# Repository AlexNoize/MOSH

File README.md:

# MOSH
#### Arduino Project in 5th year ISS at INSA Toulouse

## Overview
This repository contains the work produced during the course of Microcontroler and Open-Source Hardware (MOSH) of the 5th year Innovative Smart Systems (ISS) at INSA Toulouse. This work was produced by Alex Noize and Mathieu Raynaud.

The aim of this project was to design a complete PCB (Printed Circuit Board) implementing a double layer transimpedance amplificator assembly. This circuit is then used plugged to an Arduino board and a LoRa antenna to collect data from a gaz sensor and send it through a LoRa network. The project is located [here](https://github.com/AlexNoize/MOSH/tree/master/KiCad/Shield_Gas_Sensor/Shield_Gas_Sensor_Final)

## PCB schematic
Let's first have a look to the electrical circuit:

On the center of the image, the double layer transimpedance circuit implements several functionalities: 
* On the left of the scheme, the entry resistor (R1) protect the operational amplifier from the electrostatic discharges, and is associated to the C1 capacitor to filter the voltage noise.
* The C1 capacitor is also associated to the R2 resistor to filter the current noise.
* The R3 resistor is used to adapt our assembly to the correct calibre.
* At the output of the amplifier, the C2 capacitor is associated to the R4 resistor to create an active filter.
* Then, the R5 resistor and the C4 capacitor constitute a low-pass filter at the output of the assembly.
* Finally, the C3 capacitor filter the noise coming from the 5V voltage input.

We also have 3 other schemes on the picture which are:
* The RN2483 LoRa transceiver scheme on the left-top of the scheme
* The gas sensor scheme on the top of the scheme
* The Arduino Uno shield schematic on the right of the scheme
These components are required on the scheme because they need to be considered as soon as our PCB needs to communicate with them.

## PCB footprint on KiCad
Now, let's study the footprint generated with KiCad:

On the footprint above, we made the connections between all the needed pins of our board.

To be able to put our routes on only one face of the PCB, we had to add a ground layer on the entire surface of the PCB, so that we didn't need anymore to connect the ground-connected pins each others. This was also done for economical purposes.

Finally, we can see that two pairs of pins are still not connected on the footprint. In fact, these are two pairs of pins which are directly connected to the Arduino, and they have the same potential but they are already connected through the Arduino Uno.

## PCB 3D view
Finally, here are the generated 3D views for our PCB:

## Conclusion
The knowledge acquired during our courses allowed us to create with KiCad a PCB able to be plugged on an Arduino Uno, and to receive a gas sensor and a LoRa transceiver.

Now the next step is the print of the PCB and the creation of the gas sensor to implement the complete system.

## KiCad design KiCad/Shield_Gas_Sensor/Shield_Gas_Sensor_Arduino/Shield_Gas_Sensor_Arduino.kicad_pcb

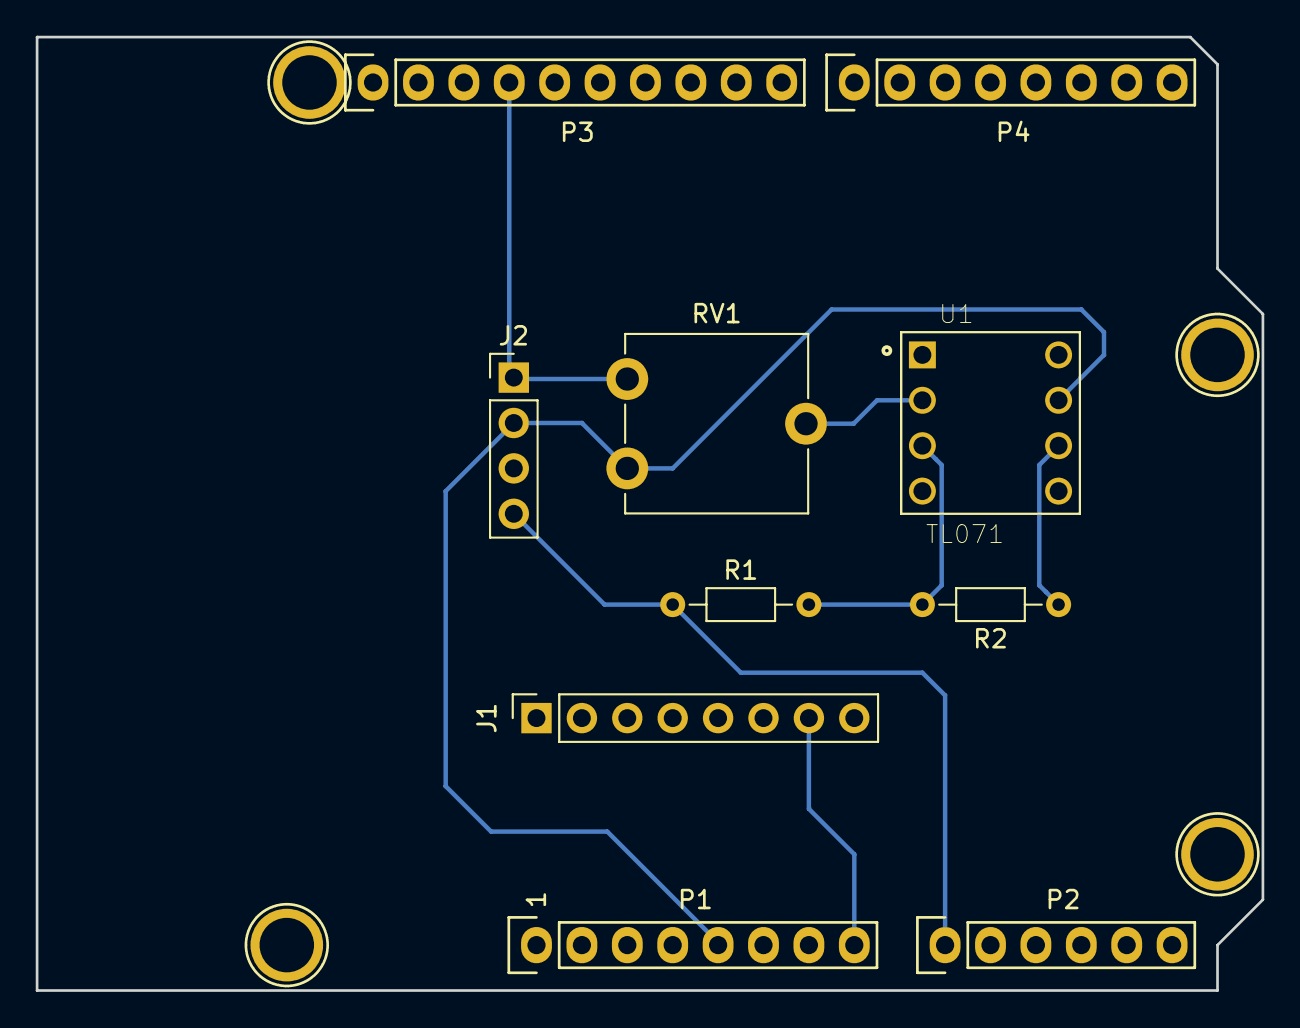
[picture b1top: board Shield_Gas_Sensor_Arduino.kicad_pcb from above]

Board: 2 copper layers, 68.6 x 53.3 mm, 14 parts (0 on the bottom side), 9 nets.

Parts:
J1: CONN_01X08; PinSocket_1x08_P2.54mm_Vertical
J2: CONN_01X04_MALE; PinHeader_1x04_P2.54mm_Vertical
P1: Power; Socket_Strip_Arduino_1x08
P2: Analog; Socket_Strip_Arduino_1x06
P3: Digital; Socket_Strip_Arduino_1x10
P4: Digital; Socket_Strip_Arduino_1x08
P5, P6, P7, P8: CONN_01X01; Arduino_1pin
R1: 4.7k; R_Axial_DIN0204_L3.6mm_D1.6mm_P7.62mm_Horizontal
R2: 100k; R_Axial_DIN0204_L3.6mm_D1.6mm_P7.62mm_Horizontal
RV1: 10k; Potentiometer_ACP_CA9-V10_Vertical
U1: TL071; TE_1-2199298-2

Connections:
+5V: J2.2, P1.5, RV1.1, U1.7
/A0: J2.4, P2.1, R1.1
/A4(SDA): P2.5, P3.2
/A5(SCL): P2.6, P3.1
/Vin: J1.7, P1.8
GND: J1.8, J2.1, P1.6, P1.7, P3.4, RV1.3, U1.4
unnamed: R1.2, R2.2, U1.3
unnamed: R2.1, U1.6
unnamed: RV1.2, U1.2

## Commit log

2018-10-22 1st commit MOSH
2018-10-22 Ajout simu spice
2018-10-22 Ajout gestion interruption
2018-10-22 maj KiCad - Ajout buzzer et bouton reset
2018-10-31 Routage PCB on Kicad
2018-10-31 Ajout Test_Buzzer (/!\ A TESTER)
2018-10-31 Début ajout shield RN2483
2018-10-31 routing not finished
2018-11-12 Routing final card
2018-11-14 14/11/2018 commit
2018-11-27 Maj before readme
2018-11-27 Adding screens
2018-11-28 Correction Tx/Rx and Screens
